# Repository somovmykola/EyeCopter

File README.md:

<h1> Group 13 Capstone </h1>

<h2> 3D Modelling Quadcopter </h2>
A large scale three dimensional scanner

<h3> Members </h3>
Paul Correia <br>
Nicolas Lelievre <br>
Bennett Mackenzie <br>
Tigran Martikian <br>
Balraj Shah <br>
Mykola Somov <br>

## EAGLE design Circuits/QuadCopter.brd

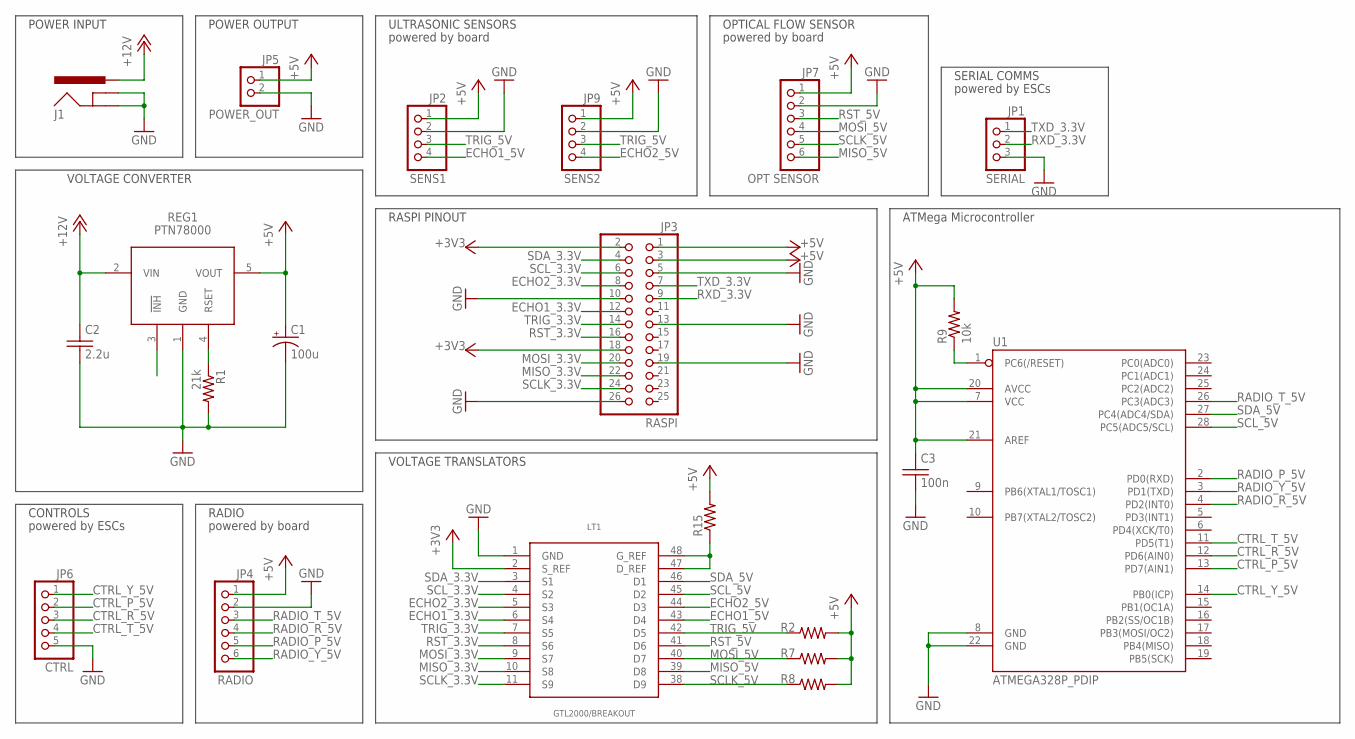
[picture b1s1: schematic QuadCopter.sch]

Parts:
C1: 100u; 153CLV-0605
C2: 2.2u; C050-025X075
C3: 100n; C050-025X075
J1: POWER_JACKSLT; POWER_JACK_SLOT
JP1: SERIAL; 1X03
JP2: SENS1; 1X04
JP3: RASPI; 2X13/SMD
JP4: RADIO; 1X06
JP5: POWER_OUT; 1X02
JP6: CTRL; 1X05
JP7: OPT SENSOR; 1X06
JP9: SENS2; 1X04
LT1: GTL2000/BREAKOUT; TSSOP48/BREAKOUT
R1: 21k; 0207/10
R2, R7, R8: R-US_0207/12; 0207/12
R9: 10k; 0207/10
R15: R-US_0207/10; 0207/10
REG1: PTN78000
U1: ATMEGA328P_PDIP; DIL28-3

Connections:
+3V3: JP3.2, JP3.18, LT1.2 (S_REF)
+5V: C1.+, C3.1, JP2.1, JP3.1, JP3.3, JP4.1, JP5.1, JP7.1, JP9.1, R2.2, R7.2, R8.2, R9.2, R15.2, REG1.5 (VOUT), U1.7 (VCC), U1.20 (AVCC), U1.21 (AREF)
+12V: C2.1, J1.PWR, REG1.2 (VIN)
CTRL_P_5V: JP6.2, U1.13 (PD7(AIN1))
CTRL_R_5V: JP6.3, U1.12 (PD6(AIN0))
CTRL_T_5V: JP6.4, U1.11 (PD5(T1))
CTRL_Y_5V: JP6.1, U1.14 (PB0(ICP))
ECHO1_3.3V: JP3.12, LT1.6 (S4)
ECHO1_5V: JP2.4, LT1.43 (D4)
ECHO2_3.3V: JP3.8, LT1.5 (S3)
ECHO2_5V: JP9.4, LT1.44 (D3)
GND: C1.-, C2.2, C3.2, J1.GND@1 (GNDBREAK), J1.GND@2 (GND), JP1.3, JP2.2, JP3.5, JP3.10, JP3.13, JP3.19, JP3.26, JP4.2, JP5.2, JP6.5, JP7.2, JP9.2, LT1.1 (GND), R1.2, REG1.1 (GND), U1.8 (GND), U1.22 (GND)
MISO_3.3V: JP3.22, LT1.10 (S8)
MISO_5V: JP7.6, LT1.39 (D8)
MOSI_3.3V: JP3.20, LT1.9 (S7)
MOSI_5V: JP7.4, LT1.40 (D7), R7.1
unnamed: LT1.47 (D_REF), LT1.48 (G_REF), R15.1
unnamed: R1.1, REG1.4 (RSET)
unnamed: R9.1, U1.1 (PC6(/RESET))
RADIO_P_5V: JP4.5, U1.2 (PD0(RXD))
RADIO_R_5V: JP4.4, U1.4 (PD2(INT0))
RADIO_T_5V: JP4.3, U1.26 (PC3(ADC3))
RADIO_Y_5V: JP4.6, U1.3 (PD1(TXD))
RST_3.3V: JP3.16, LT1.8 (S6)
RST_5V: JP7.3, LT1.41 (D6)
RXD_3.3V: JP1.2, JP3.9
SCLK_3.3V: JP3.24, LT1.11 (S9)
SCLK_5V: JP7.5, LT1.38 (D9), R8.1
SCL_3.3V: JP3.6, LT1.4 (S2)
SCL_5V: LT1.45 (D2), U1.28 (PC5(ADC5/SCL))
SDA_3.3V: JP3.4, LT1.3 (S1)
SDA_5V: LT1.46 (D1), U1.27 (PC4(ADC4/SDA))
TRIG_3.3V: JP3.14, LT1.7 (S5)
TRIG_5V: JP2.3, JP9.3, LT1.42 (D5), R2.1
TXD_3.3V: JP1.1, JP3.7

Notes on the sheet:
ULTRASONIC SENSORS
RADIO
CONTROLS
VOLTAGE TRANSLATORS
RASPI PINOUT
SERIAL COMMS
POWER OUTPUT
POWER INPUT
VOLTAGE CONVERTER
OPTICAL FLOW SENSOR
powered by board
powered by ESCs
ATMega Microcontroller

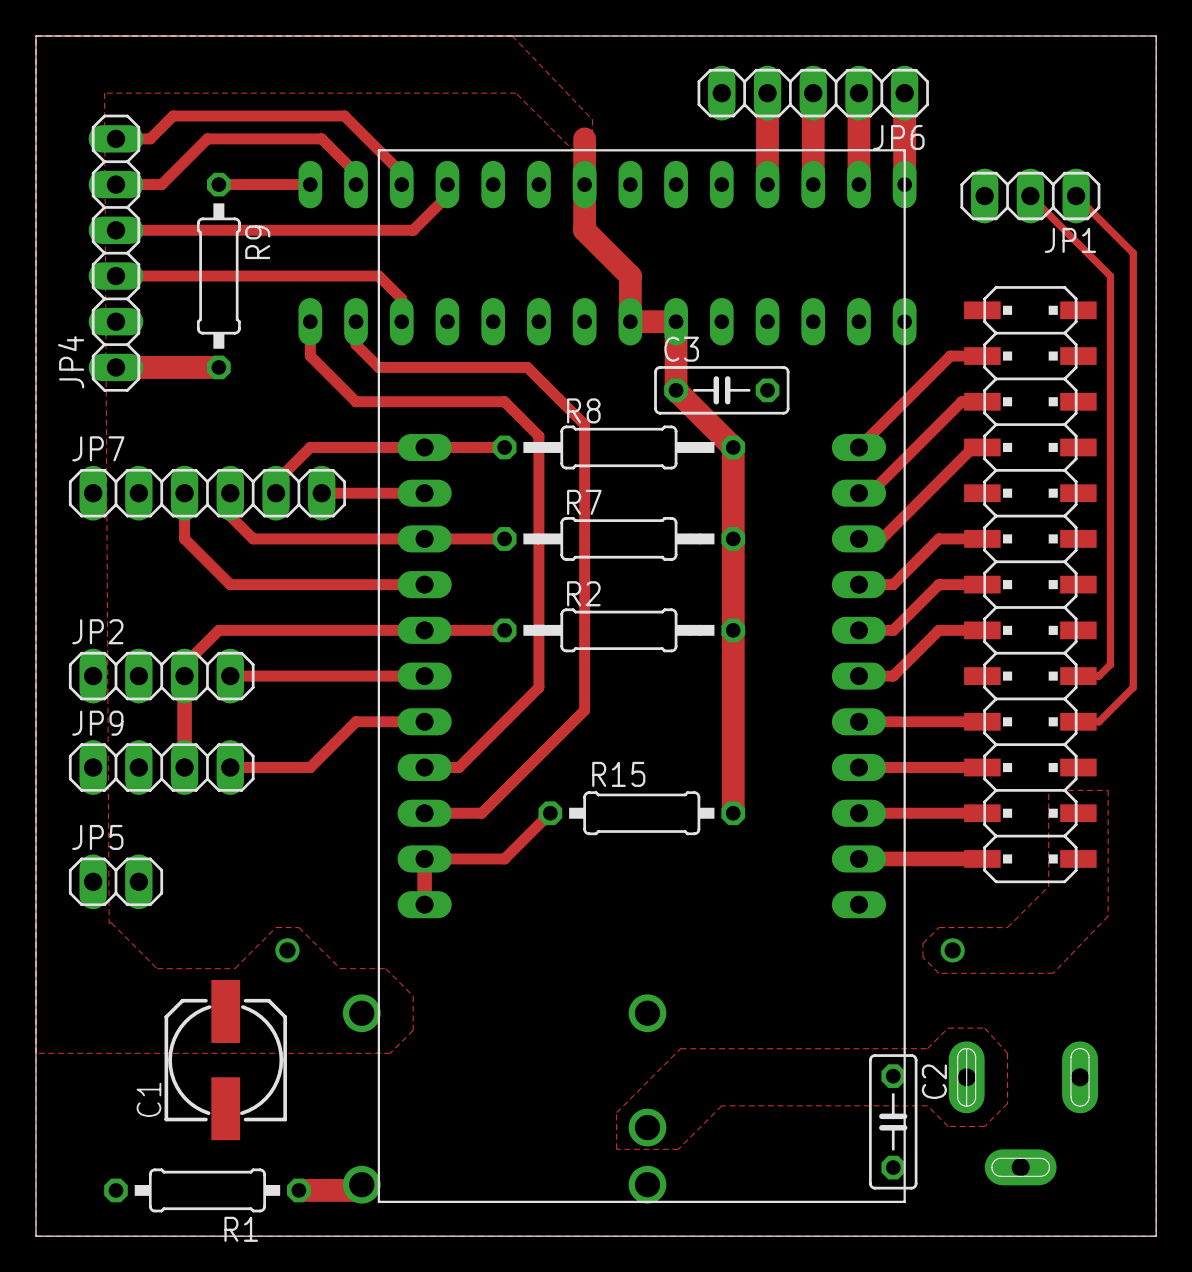
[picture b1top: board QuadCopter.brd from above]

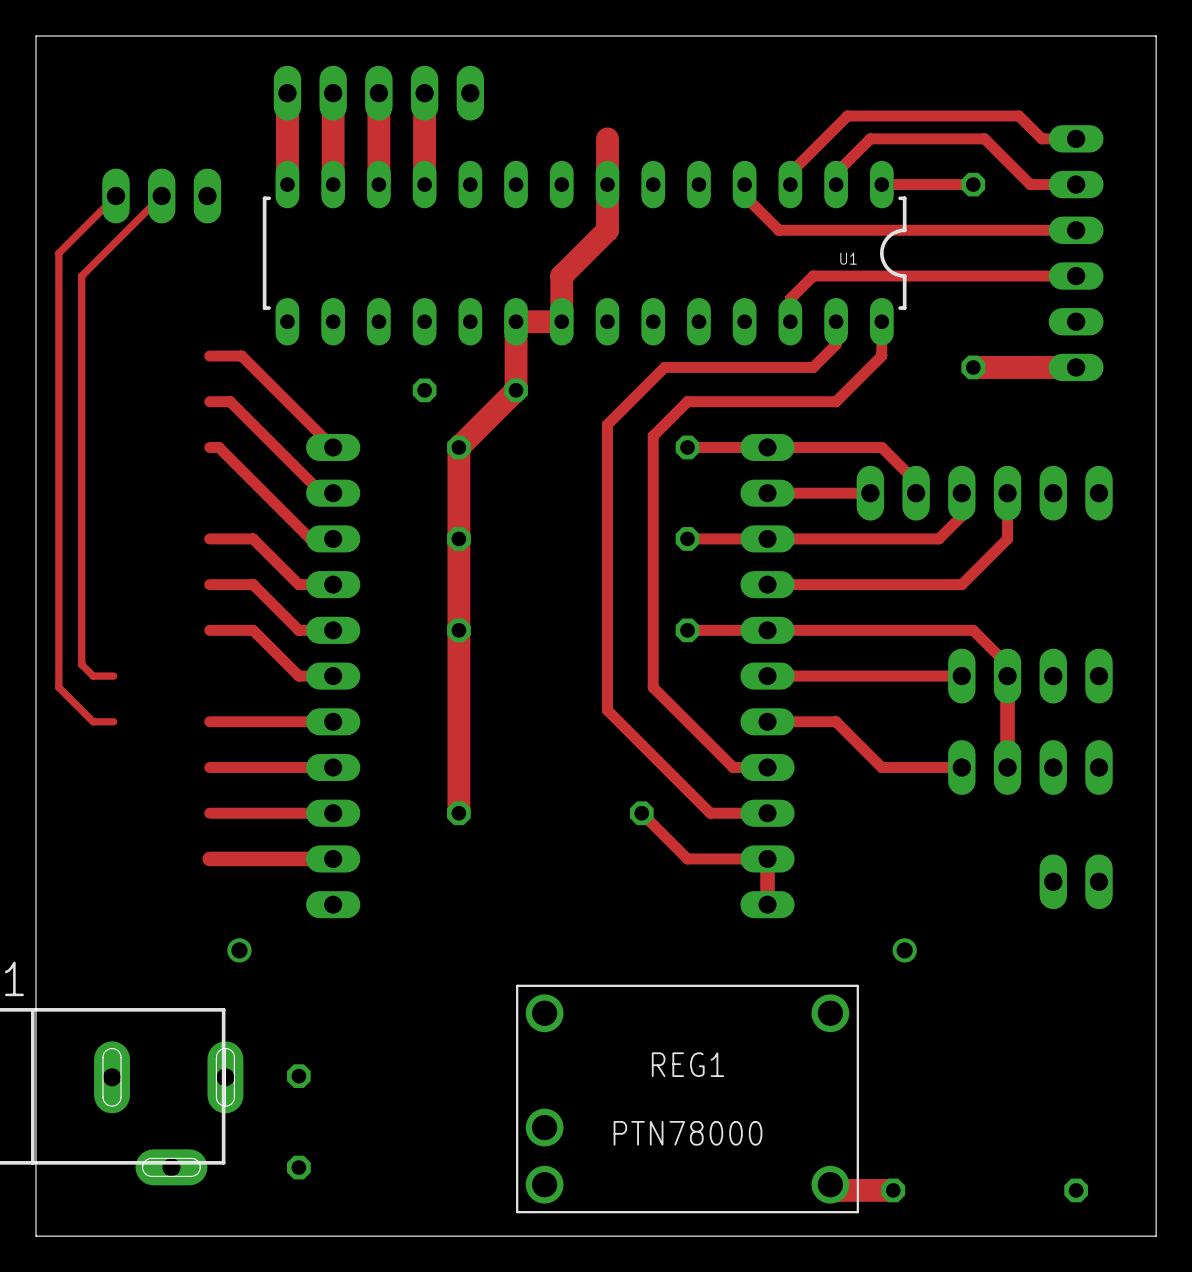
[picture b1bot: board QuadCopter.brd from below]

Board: 2 copper layers, 62.2 x 66.7 mm, 21 parts (3 on the bottom side), 35 nets.

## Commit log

2016-05-02 eyecopter project, practical flight not tested

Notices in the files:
parts and their libraries:
SparkFun-Connectors: Licensing: Creative Commons ShareAlike 4.0 International - https://creativecommons.org/licenses/by-sa/4.0
